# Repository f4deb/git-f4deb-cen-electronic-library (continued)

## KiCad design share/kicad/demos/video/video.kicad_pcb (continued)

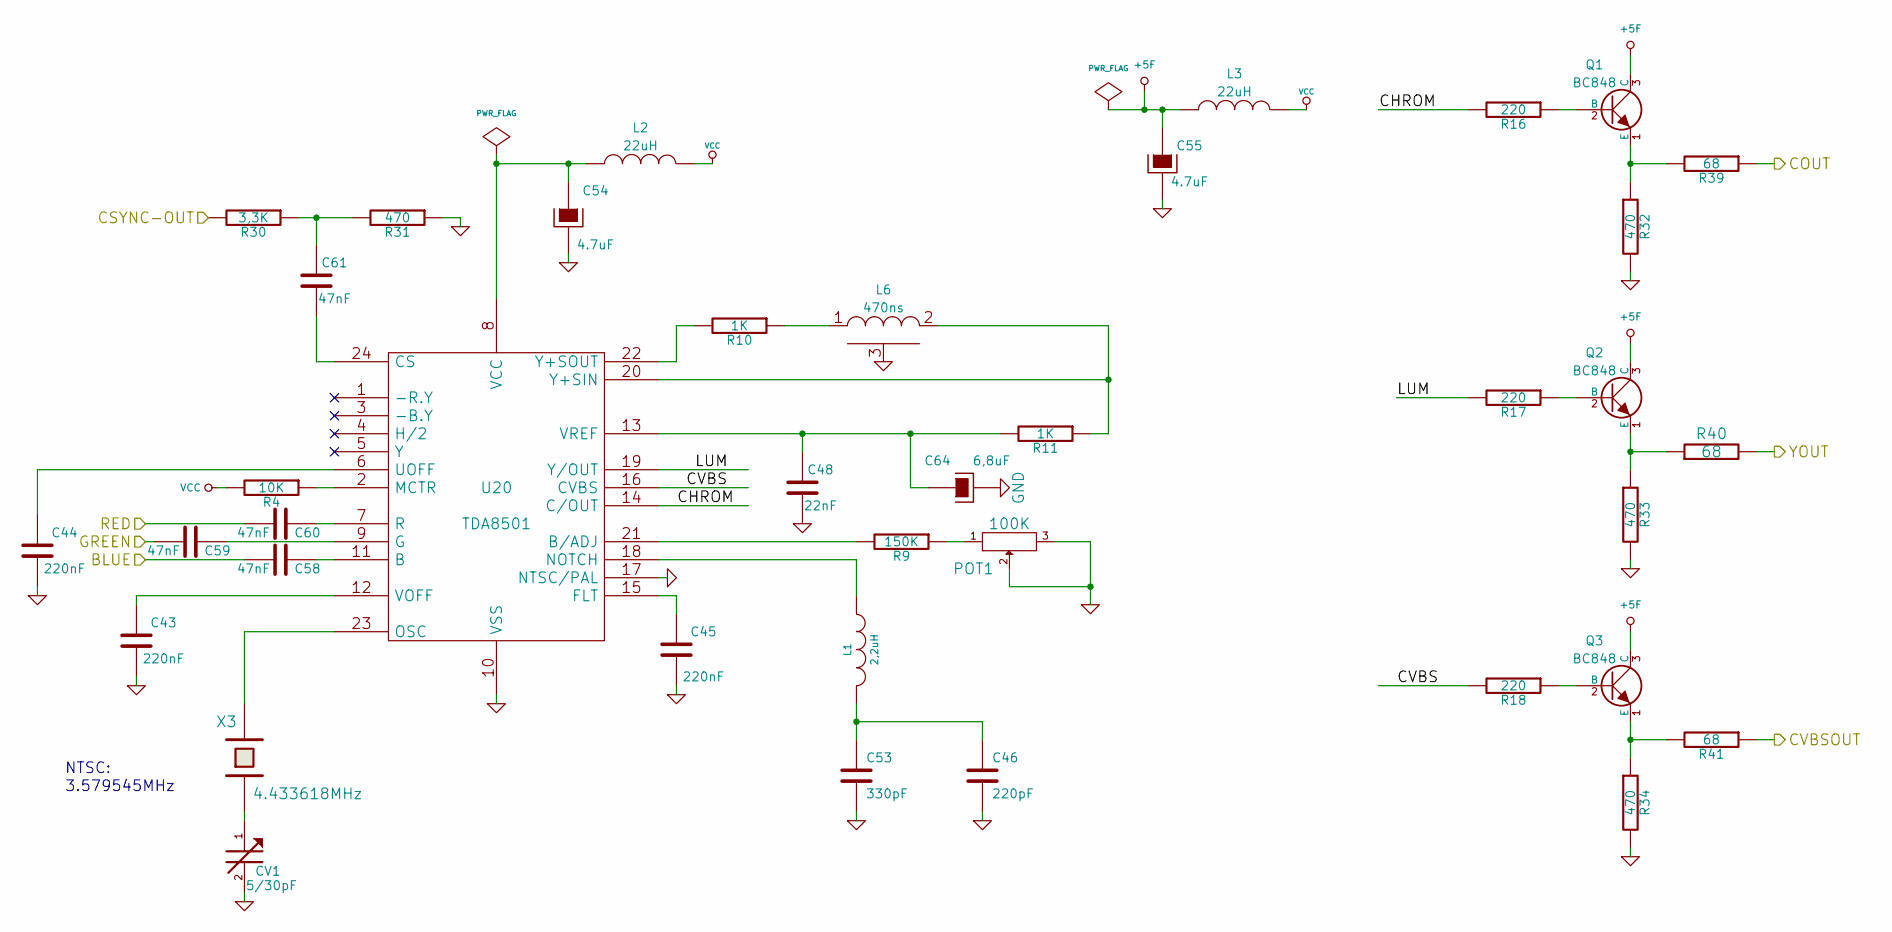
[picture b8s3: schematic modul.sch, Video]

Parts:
C43, C44, C45: 220nF; SM1206
C46: 220pF; SM1206
C48: 22nF; SM1206
C53: 330pF; SM1206
C54: 4.7uF; SM1206
C55: 4.7uF; SM1210L
C58, C59, C60, C61: 47nF; SM1206
C64: 6,8uF; SM1210L
CV1: 5/30pF; CV3-30PF
L1: 2,2uH; SM1812
L2, L3: 22uH; SM1812
L6: 470ns; LRTDK
POT1: 100K; POT_CMS
Q1, Q2, Q3: BC848; SOT23EBC
R4: 10K; SM1206
R9: 150K; SM1206
R10, R11: 1K; SM1206
R16, R17, R18: 220; SM1206
R30: 3,3K; SM1206
R31, R32, R33, R34: 470; SM1206
R39, R40, R41: 68; SM1206
U20: TDA8501; SO24E
X3: 4.433618MHz; HC-18UH

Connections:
+5F: C55.1, L3.2, Q1.3 (C), Q2.3 (C), Q3.3 (C)
/ESVIDEO-RVB/BLUE: C60.2; also elsewhere on the board
/ESVIDEO-RVB/GREEN: C59.2; also elsewhere on the board
/graphic/CSYNC-OUT: R30.2; also elsewhere on the board
/modul/BLEU: C58.2; also elsewhere on the board
/modul/CHROM: R16.2, U20.14 (C/OUT)
/modul/COUT: R39.1; also elsewhere on the board
/modul/CVBS: R18.2, U20.16 (CVBS)
/modul/CVBSOUT: R41.1; also elsewhere on the board
/modul/LUM: R17.2, U20.19 (Y/OUT)
/modul/YOUT: R40.2; also elsewhere on the board
GND: C43.2, C44.2, C45.2, C46.2, C48.1, C53.2, C54.2, C55.2, C64.2, CV1.2, L6.3 (COMMUN), POT1.2, POT1.3, R31.1, R32.2, R33.2, R34.2, U20.10 (VSS), U20.17 (NTSC/PAL); also elsewhere on the board
unnamed: C43.1, U20.12 (VOFF)
unnamed: C44.1, U20.6 (UOFF)
unnamed: C45.1, U20.15 (FLT)
unnamed: C46.1, C53.1, L1.2
unnamed: C48.2, C64.1, R11.2, U20.13 (VREF)
unnamed: C54.1, L2.2, U20.8 (VCC)
unnamed: C58.1, U20.11 (B)
unnamed: C59.1, U20.9 (G)
unnamed: C60.1, U20.7 (R)
unnamed: C61.1, R30.1, R31.2
unnamed: C61.2, U20.24 (CS)
unnamed: CV1.1, X3.1
unnamed: L1.1, U20.18 (NOTCH)
unnamed: L6.1, R10.1
unnamed: L6.2, R11.1, U20.20 (Y+SIN)
unnamed: POT1.1, R9.1
unnamed: Q1.1 (E), R32.1, R39.2
unnamed: Q1.2 (B), R16.1
unnamed: Q2.1 (E), R33.1, R40.1
unnamed: Q2.2 (B), R17.1
unnamed: Q3.1 (E), R34.1, R41.2
unnamed: Q3.2 (B), R18.1
unnamed: R4.1, U20.2 (MCTR)
unnamed: R9.2, U20.21 (B/ADJ)
unnamed: R10.2, U20.22 (Y+SOUT)
unnamed: U20.23 (OSC), X3.2
VCC: L2.1, L3.1, R4.2; also elsewhere on the board

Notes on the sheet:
NTSC:
3.579545MHz

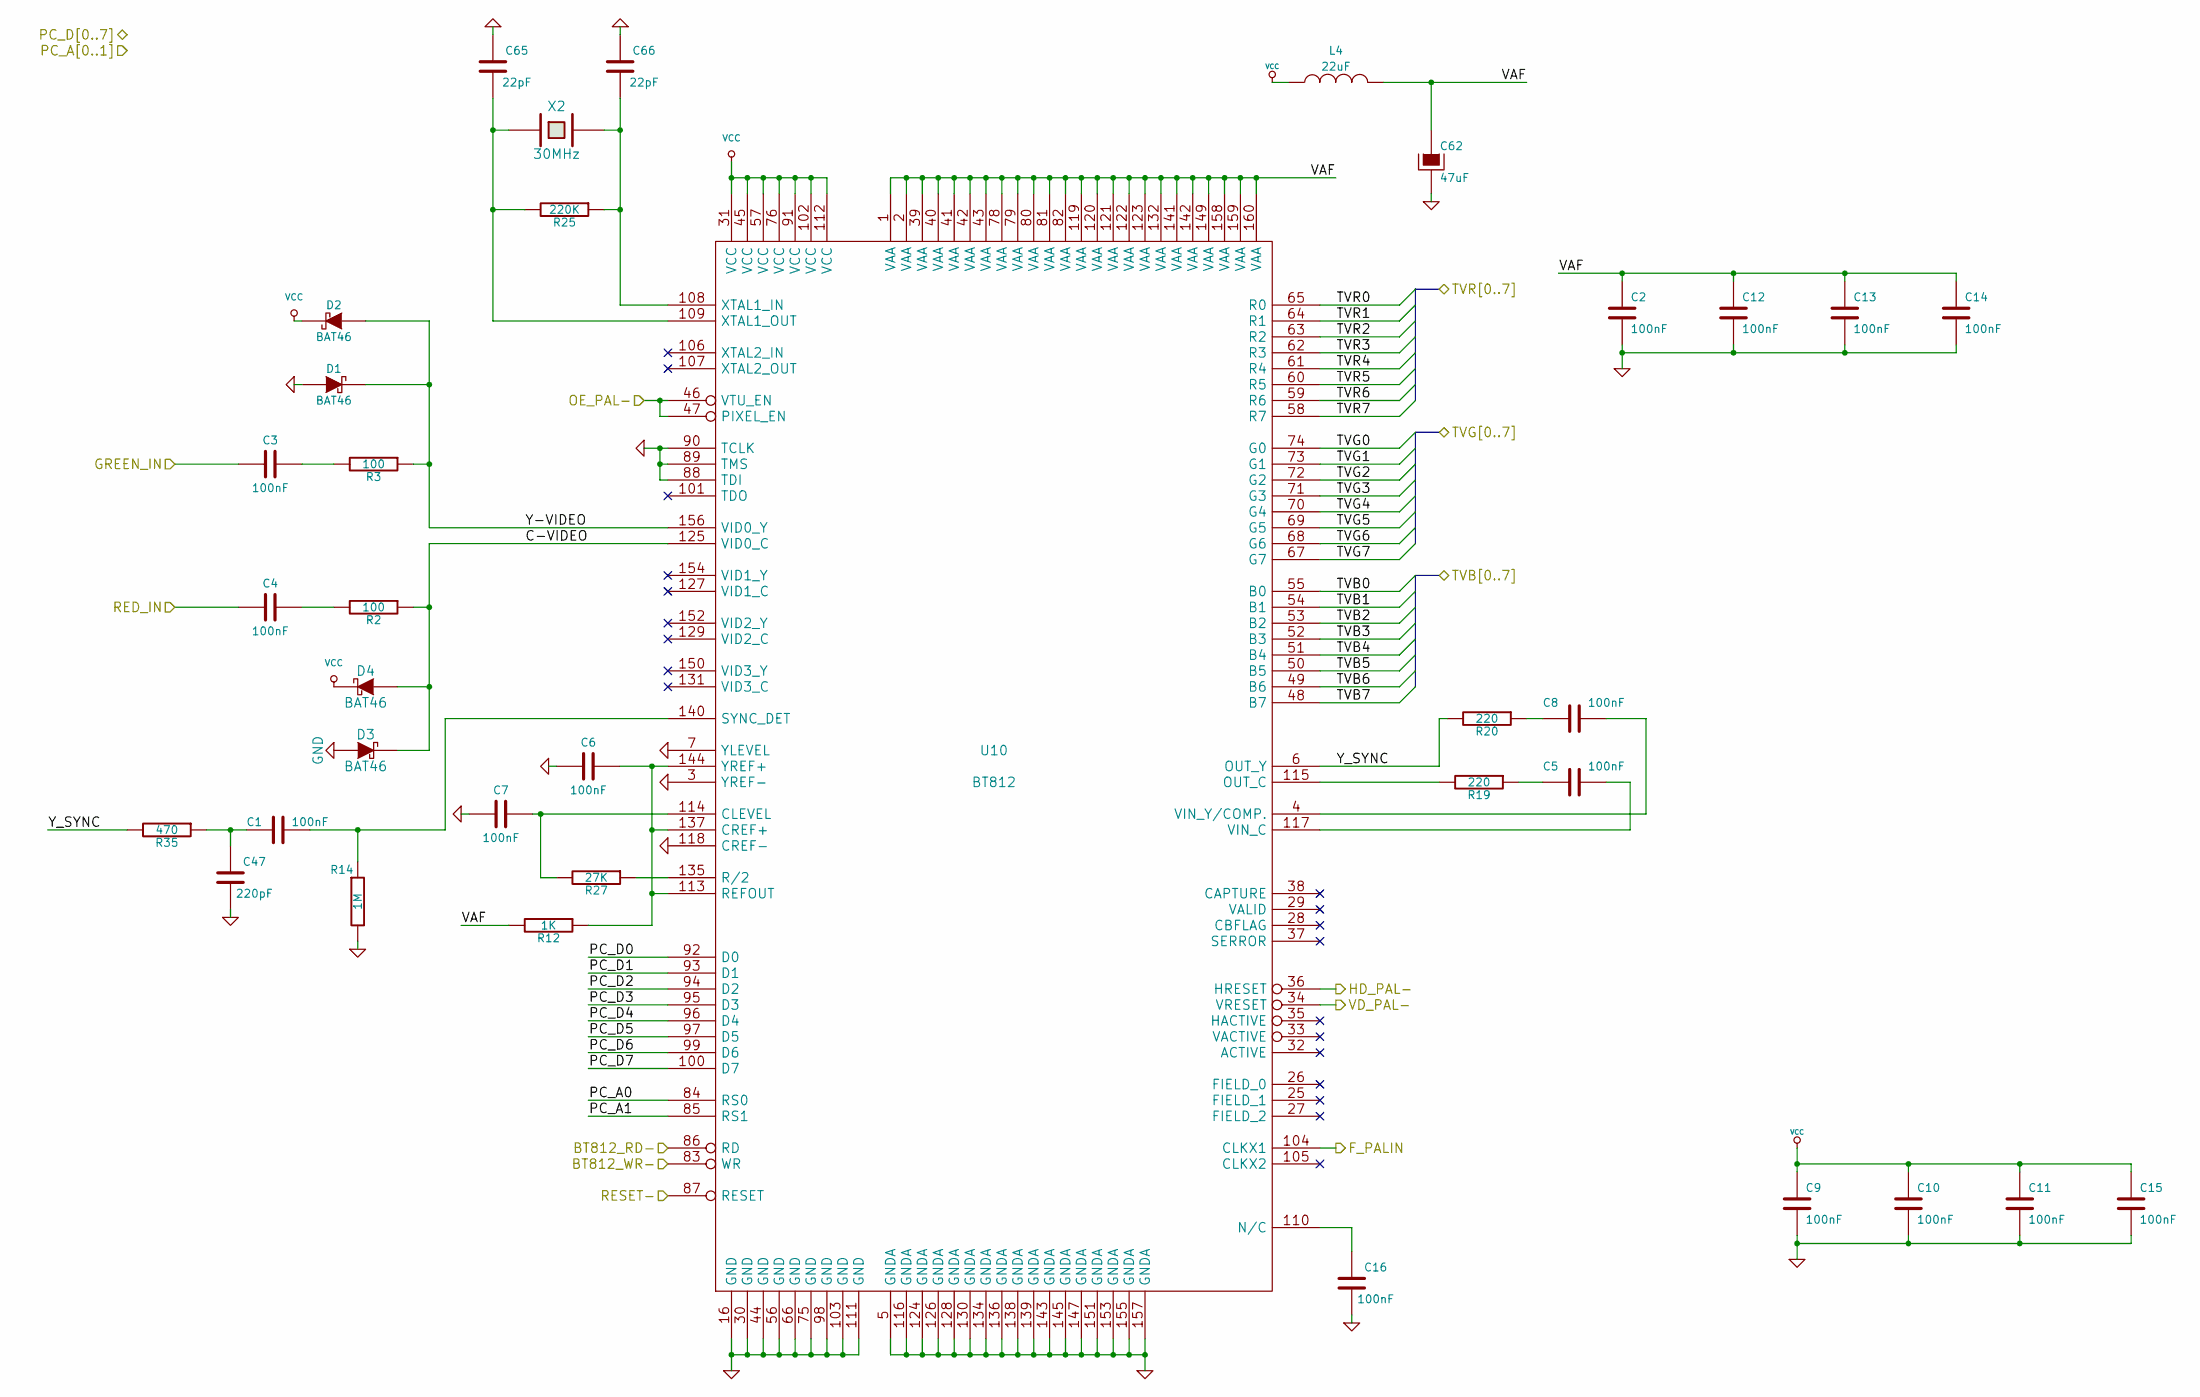
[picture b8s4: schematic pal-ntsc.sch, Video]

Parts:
C1, C2, C3, C4, C5, C6, C7, C8, C9, C10, C11, C12, C13, C14, C15, C16: 100nF; SM1206
C47: 220pF; SM1206
C62: 47uF; SM1210L
C65, C66: 22pF; SM1206
D1, D2, D3, D4: BAT46; D3
L4: 22uF; SM1812
R2, R3: 100; SM1206
R12: 1K; SM1206
R14: 1M; SM1206
R19, R20: 220; SM1206
R25: 220K; SM1206
R27: 27K; SM1206
R35: 470; SM1206
U10: BT812; PQFP160
X2: 30MHz; HC-18UV

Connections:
/ESVIDEO-RVB/DPC0: U10.92 (D0); also elsewhere on the board
/ESVIDEO-RVB/DPC1: U10.93 (D1); also elsewhere on the board
/ESVIDEO-RVB/DPC2: U10.94 (D2); also elsewhere on the board
/ESVIDEO-RVB/DPC3: U10.95 (D3); also elsewhere on the board
/ESVIDEO-RVB/DPC4: U10.96 (D4); also elsewhere on the board
/ESVIDEO-RVB/DPC5: U10.97 (D5); also elsewhere on the board
/ESVIDEO-RVB/DPC6: U10.99 (D6); also elsewhere on the board
/ESVIDEO-RVB/DPC7: U10.100 (D7); also elsewhere on the board
/ESVIDEO-RVB/GREEN_IN: C3.2; also elsewhere on the board
/ESVIDEO-RVB/OE_PAL-: U10.46 (VTU_EN), U10.47 (PIXEL_EN); also elsewhere on the board
/ESVIDEO-RVB/PCA0: U10.84 (RS0); also elsewhere on the board
/ESVIDEO-RVB/PCA1: U10.85 (RS1); also elsewhere on the board
/ESVIDEO-RVB/RED_IN: C4.2; also elsewhere on the board
/ESVIDEO-RVB/TVB0: U10.55 (B0); also elsewhere on the board
/ESVIDEO-RVB/TVB1: U10.54 (B1); also elsewhere on the board
/ESVIDEO-RVB/TVB2: U10.53 (B2); also elsewhere on the board
/ESVIDEO-RVB/TVB3: U10.52 (B3); also elsewhere on the board
/ESVIDEO-RVB/TVB4: U10.51 (B4); also elsewhere on the board
/ESVIDEO-RVB/TVB5: U10.50 (B5); also elsewhere on the board
/ESVIDEO-RVB/TVB6: U10.49 (B6); also elsewhere on the board
/ESVIDEO-RVB/TVB7: U10.48 (B7); also elsewhere on the board
/ESVIDEO-RVB/TVG0: U10.74 (G0); also elsewhere on the board
/ESVIDEO-RVB/TVG1: U10.73 (G1); also elsewhere on the board
/ESVIDEO-RVB/TVG2: U10.72 (G2); also elsewhere on the board
/ESVIDEO-RVB/TVG3: U10.71 (G3); also elsewhere on the board
/ESVIDEO-RVB/TVG4: U10.70 (G4); also elsewhere on the board
/ESVIDEO-RVB/TVG5: U10.69 (G5); also elsewhere on the board
/ESVIDEO-RVB/TVG6: U10.68 (G6); also elsewhere on the board
/ESVIDEO-RVB/TVG7: U10.67 (G7); also elsewhere on the board
/ESVIDEO-RVB/TVR0: U10.65 (R0); also elsewhere on the board
/ESVIDEO-RVB/TVR1: U10.64 (R1); also elsewhere on the board
/ESVIDEO-RVB/TVR2: U10.63 (R2); also elsewhere on the board
/ESVIDEO-RVB/TVR3: U10.62 (R3); also elsewhere on the board
/ESVIDEO-RVB/TVR4: U10.61 (R4); also elsewhere on the board
/ESVIDEO-RVB/TVR5: U10.60 (R5); also elsewhere on the board
/ESVIDEO-RVB/TVR6: U10.59 (R6); also elsewhere on the board
/ESVIDEO-RVB/TVR7: U10.58 (R7); also elsewhere on the board
/graphic/BT812_RD-: U10.86 (RD); also elsewhere on the board
/graphic/BT812_WR-: U10.83 (WR); also elsewhere on the board
/graphic/F_PALIN: U10.104 (CLKX1); also elsewhere on the board
/graphic/HD_PAL-: U10.36 (HRESET); also elsewhere on the board
/graphic/VD_PAL-: U10.34 (VRESET); also elsewhere on the board
/pal-ntsc.sch/C-VIDEO: D3.2 (K), D4.1 (A), R2.1, U10.125 (VID0_C)
/pal-ntsc.sch/RESET-: U10.87 (RESET); also elsewhere on the board
/pal-ntsc.sch/VAF: C2.1, C12.1, C13.1, C14.1, C62.1, L4.2, R12.2, U10.1 (VAA), U10.2 (VAA), U10.39 (VAA), U10.40 (VAA), U10.41 (VAA), U10.42 (VAA), U10.43 (VAA), U10.78 (VAA), U10.79 (VAA), U10.80 (VAA), U10.81 (VAA), U10.82 (VAA), U10.119 (VAA), U10.120 (VAA), U10.121 (VAA), U10.122 (VAA), U10.123 (VAA), U10.132 (VAA), U10.141 (VAA), U10.142 (VAA), U10.149 (VAA), U10.158 (VAA), U10.159 (VAA), U10.160 (VAA)
/pal-ntsc.sch/Y-VIDEO: D1.2 (K), D2.1 (A), R3.1, U10.156 (VID0_Y)
/pal-ntsc.sch/Y_SYNC: R20.2, R35.2, U10.6 (OUT_Y)
GND: C2.2, C6.2, C7.2, C9.2, C10.2, C11.2, C12.2, C13.2, C14.2, C15.2, C16.2, C47.2, C62.2, C65.1, C66.1, D1.1 (A), D3.1 (A), R14.2, U10.3 (YREF-), U10.5 (GNDA), U10.7 (YLEVEL), U10.16 (GND), U10.30 (GND), U10.44 (GND), U10.56 (GND), U10.66 (GND), U10.75 (GND), U10.88 (TDI), U10.89 (TMS), U10.90 (TCLK), U10.98 (GND), U10.103 (GND), U10.111 (GND), U10.116 (GNDA), U10.118 (CREF-), U10.124 (GNDA), U10.126 (GNDA), U10.128 (GNDA), U10.130 (GNDA), U10.134 (GNDA), U10.136 (GNDA), U10.138 (GNDA), U10.139 (GNDA), U10.143 (GNDA), U10.145 (GNDA), U10.147 (GNDA), U10.151 (GNDA), U10.153 (GNDA), U10.155 (GNDA), U10.157 (GNDA); also elsewhere on the board
unnamed: C1.1, C47.1, R35.1
unnamed: C1.2, R14.1, U10.140 (SYNC_DET)
unnamed: C3.1, R3.2
unnamed: C4.1, R2.2
unnamed: C5.1, U10.117 (VIN_C)
unnamed: C5.2, R19.1
unnamed: C6.1, R12.1, U10.113 (REFOUT), U10.137 (CREF+), U10.144 (YREF+)
unnamed: C7.1, R27.2, U10.114 (CLEVEL)
unnamed: C8.1, U10.4 (VIN_Y/COMP.)
unnamed: C8.2, R20.1
unnamed: C16.1, U10.110 (N/C)
unnamed: C65.2, R25.2, U10.109 (XTAL1_OUT), X2.1
unnamed: C66.2, R25.1, U10.108 (XTAL1_IN), X2.2
unnamed: R19.2, U10.115 (OUT_C)
unnamed: R27.1, U10.135 (R/2)
VCC: C9.1, C10.1, C11.1, C15.1, D2.2 (K), D4.2 (K), L4.1, U10.31 (VCC), U10.45 (VCC), U10.57 (VCC), U10.76 (VCC), U10.91 (VCC), U10.102 (VCC), U10.112 (VCC); also elsewhere on the board

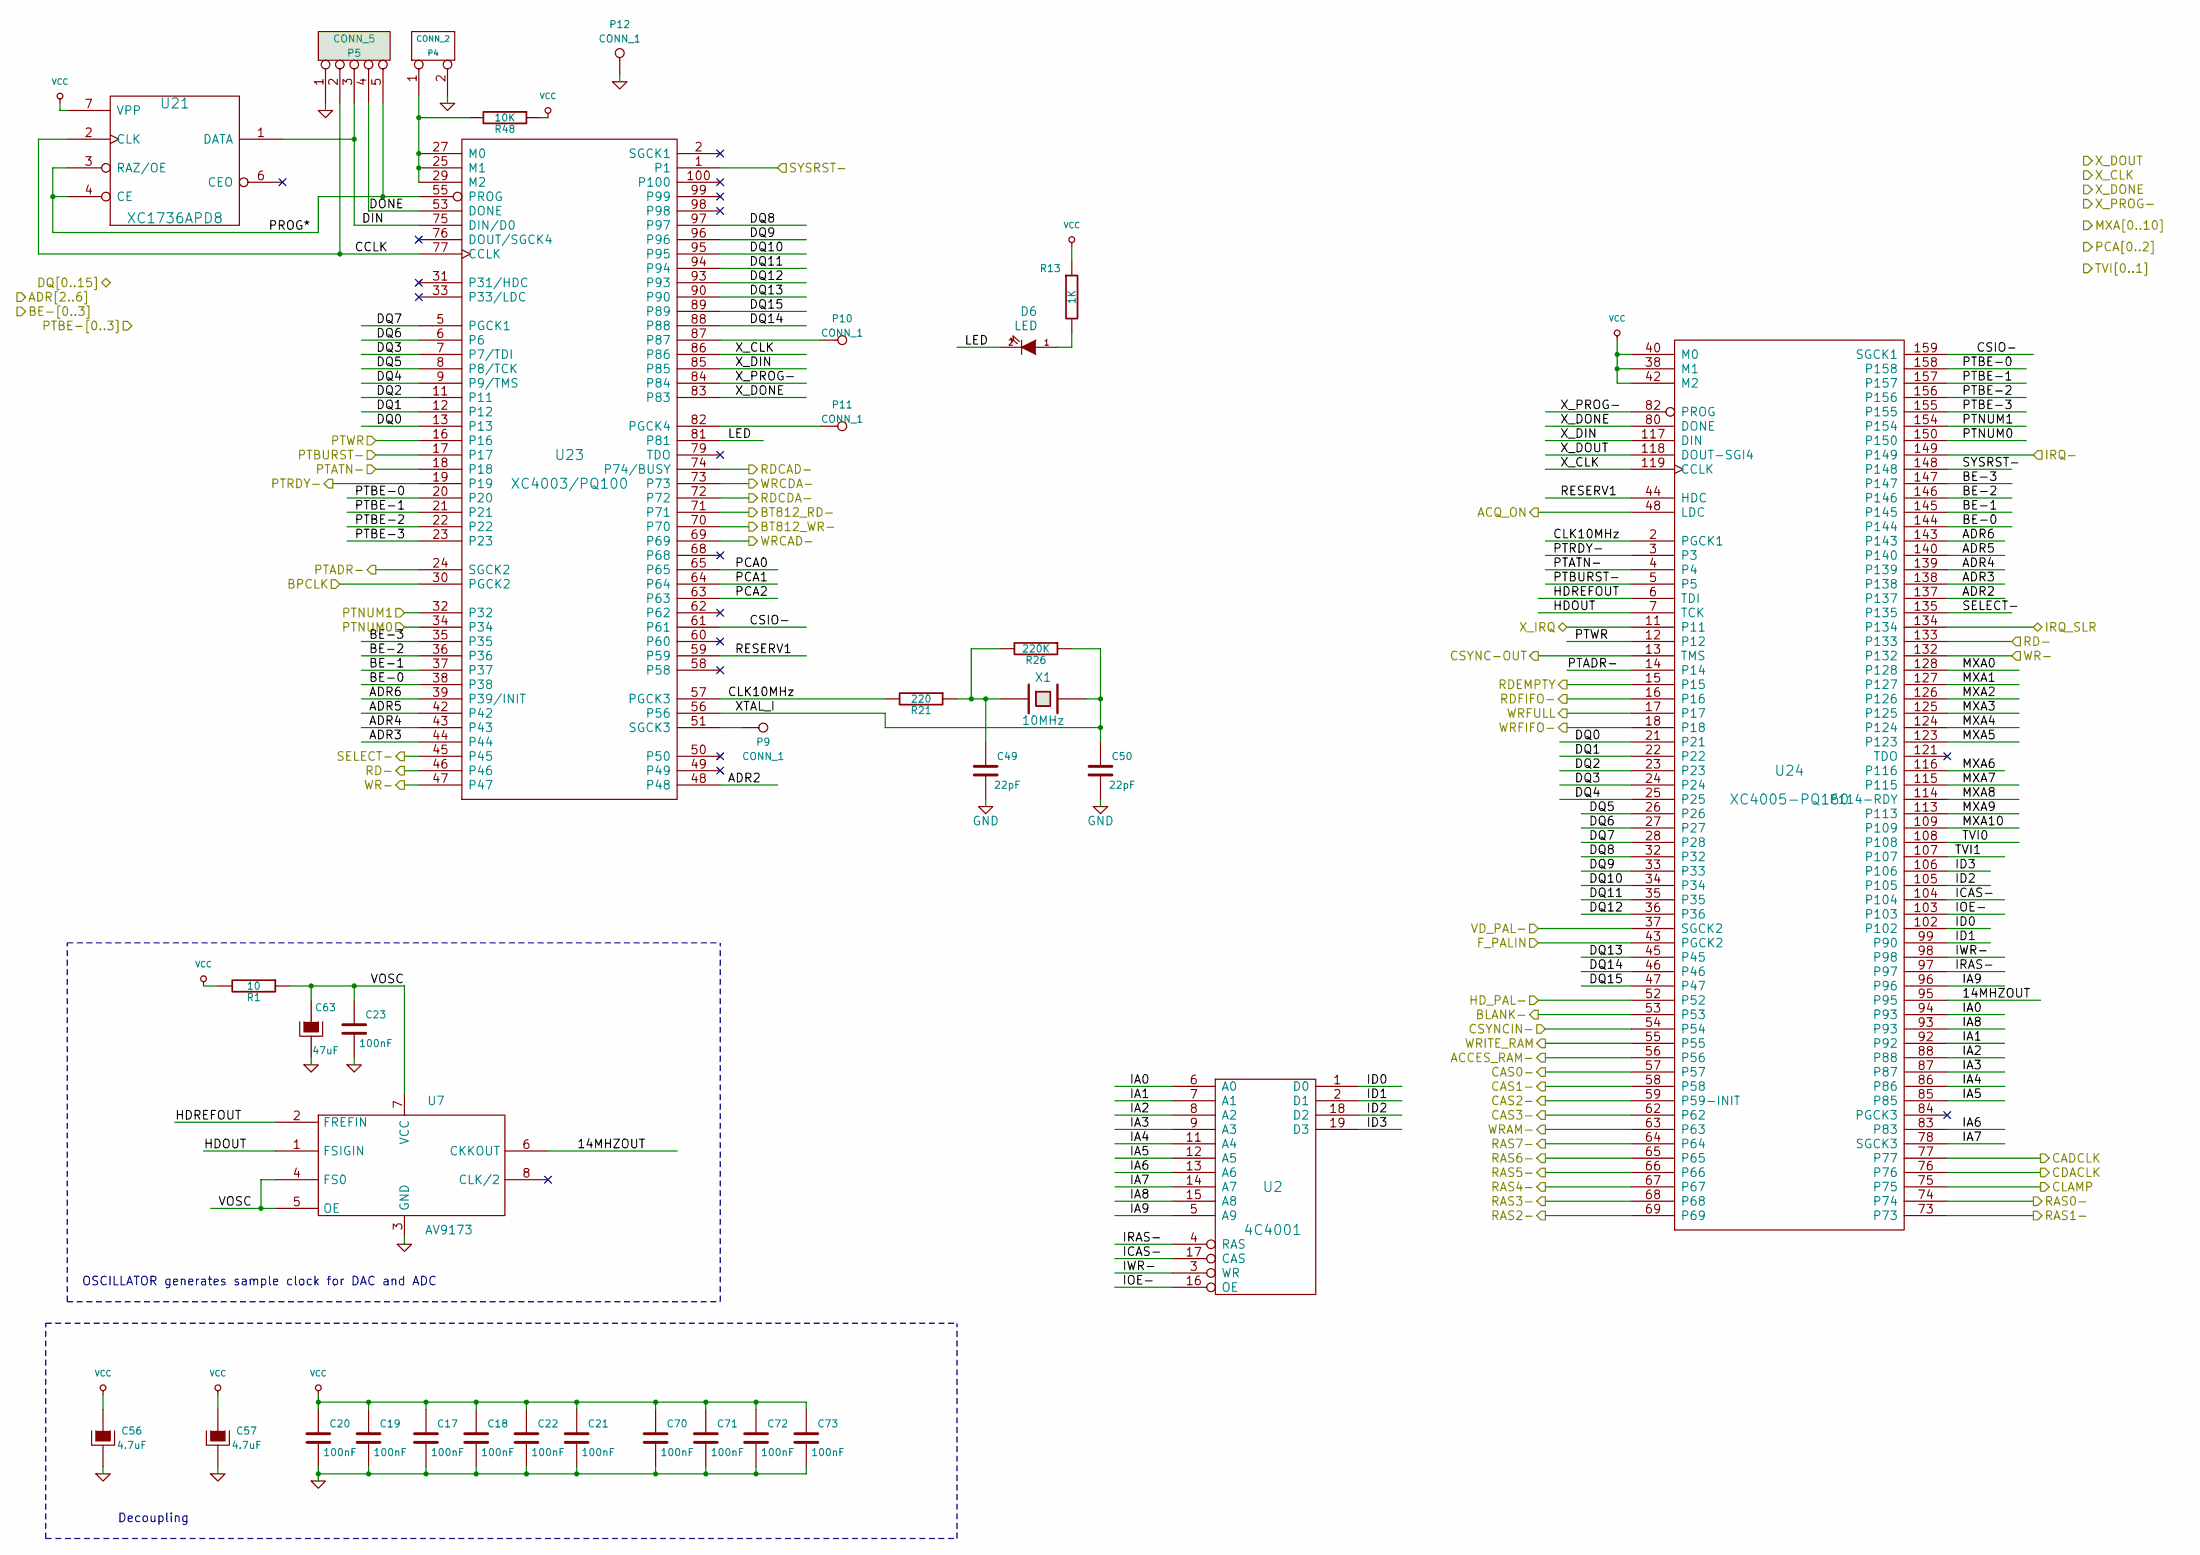
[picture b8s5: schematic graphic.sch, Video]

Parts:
C17, C18, C19, C20, C21, C22, C23, C70, C71, C72, C73: 100nF; SM1206
C49, C50: 22pF; C1
C56: 4.7uF; SM1812L
C57: 4.7uF; SM1210L
C63: 47uF; SM1210L
D6: LED; LEDV
P4: CONN_2; SIL-2
P5: CONN_5; PIN_ARRAY_5x1
P9, P10, P11: CONN_1; PINTST
P12: CONN_1; TESTPOINT
R1: 10; SM1206
R13: 1K; SM1206
R21: 220; SM1206
R26: 220K; SM1206
R48: 10K; SM1206
U2: 4C4001; SO28
U7: AV9173; SO8E
U21: XC1736APD8; DIP-8__300
U23: XC4003/PQ100; PQFP100
U24: XC4005-PQ160; PQFP160
X1: 10MHz; HC-18UV

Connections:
/ESVIDEO-RVB/BLANK-: U24.53; also elsewhere on the board
/ESVIDEO-RVB/CLAMP: U24.75; also elsewhere on the board
/ESVIDEO-RVB/CSYNCIN-: U24.54; also elsewhere on the board
/ESVIDEO-RVB/DPC0: U23.13, U24.21; also elsewhere on the board
/ESVIDEO-RVB/DPC1: U23.12, U24.22; also elsewhere on the board
/ESVIDEO-RVB/DPC2: U23.11, U24.23; also elsewhere on the board
/ESVIDEO-RVB/DPC3: U23.7 (P7/TDI), U24.24; also elsewhere on the board
/ESVIDEO-RVB/DPC4: U23.9 (P9/TMS), U24.25; also elsewhere on the board
/ESVIDEO-RVB/DPC5: U23.8 (P8/TCK), U24.26; also elsewhere on the board
/ESVIDEO-RVB/DPC6: U23.6, U24.27; also elsewhere on the board
/ESVIDEO-RVB/DPC7: U23.5 (PGCK1), U24.28; also elsewhere on the board
/ESVIDEO-RVB/PCA0: U23.65; also elsewhere on the board
/ESVIDEO-RVB/PCA1: U23.64; also elsewhere on the board
/ESVIDEO-RVB/PCA2: U23.63; also elsewhere on the board
/ESVIDEO-RVB/RDCAD-: U23.74 (P74/BUSY); also elsewhere on the board
/ESVIDEO-RVB/RDCDA-: U23.72; also elsewhere on the board
/ESVIDEO-RVB/TVI0: U24.108; also elsewhere on the board
/ESVIDEO-RVB/TVI1: U24.107; also elsewhere on the board
/ESVIDEO-RVB/WRCAD-: U23.69; also elsewhere on the board
/ESVIDEO-RVB/WRCDA-: U23.73; also elsewhere on the board
/RAMS/CAS0-: U24.57; also elsewhere on the board
/RAMS/CAS1-: U24.58; also elsewhere on the board
/RAMS/CAS2-: U24.59 (P59-INIT); also elsewhere on the board
/RAMS/CAS3-: U24.62; also elsewhere on the board
/RAMS/MXA0: U24.128; also elsewhere on the board
/RAMS/MXA1: U24.127; also elsewhere on the board
/RAMS/MXA2: U24.126; also elsewhere on the board
/RAMS/MXA3: U24.125; also elsewhere on the board
/RAMS/MXA4: U24.124; also elsewhere on the board
/RAMS/MXA5: U24.123; also elsewhere on the board
/RAMS/MXA6: U24.116; also elsewhere on the board
/RAMS/MXA7: U24.115; also elsewhere on the board
/RAMS/MXA8: U24.114 (P114-RDY); also elsewhere on the board
/RAMS/MXA9: U24.113; also elsewhere on the board
/RAMS/MXA10: U24.109; also elsewhere on the board
/RAMS/RAS0-: U24.74; also elsewhere on the board
/RAMS/RAS1-: U24.73; also elsewhere on the board
/RAMS/RAS2-: U24.69; also elsewhere on the board
/RAMS/RAS3-: U24.68; also elsewhere on the board
/RAMS/RAS4-: U24.67; also elsewhere on the board
/RAMS/RAS5-: U24.66; also elsewhere on the board
/RAMS/RAS6-: U24.65; also elsewhere on the board
/RAMS/RAS7-: U24.64; also elsewhere on the board
/RAMS/WRAM-: U24.63; also elsewhere on the board
/buspci.sch/ADR2: U23.48, U24.137; also elsewhere on the board
/buspci.sch/ADR3: U23.44, U24.138; also elsewhere on the board
/buspci.sch/ADR4: U23.43, U24.139; also elsewhere on the board
/buspci.sch/ADR5: U23.42, U24.140; also elsewhere on the board
/buspci.sch/ADR6: U23.39 (P39/INIT), U24.143; also elsewhere on the board
/buspci.sch/BE-0: U23.38, U24.144; also elsewhere on the board
/buspci.sch/BE-1: U23.37, U24.145; also elsewhere on the board
/buspci.sch/BE-2: U23.36, U24.146; also elsewhere on the board
/buspci.sch/BE-3: U23.35, U24.147; also elsewhere on the board
/buspci.sch/BPCLK: U23.30 (PGCK2); also elsewhere on the board
/buspci.sch/IRQ-: U24.149; also elsewhere on the board
/buspci.sch/PTADR-: U23.24 (SGCK2), U24.14; also elsewhere on the board
/buspci.sch/PTATN-: U23.18, U24.4; also elsewhere on the board
/buspci.sch/PTBE-0: U23.20, U24.158; also elsewhere on the board
/buspci.sch/PTBE-1: U23.21, U24.157; also elsewhere on the board
/buspci.sch/PTBE-2: U23.22, U24.156; also elsewhere on the board
/buspci.sch/PTBE-3: U23.23, U24.155; also elsewhere on the board
/buspci.sch/PTBURST-: U23.17, U24.5; also elsewhere on the board
/buspci.sch/PTNUM0: U23.34, U24.150; also elsewhere on the board
/buspci.sch/PTNUM1: U23.32, U24.154; also elsewhere on the board
/buspci.sch/PTRDY-: U23.19, U24.3; also elsewhere on the board
/buspci.sch/PTWR: U23.16, U24.12; also elsewhere on the board
/buspci.sch/RD-: U23.46, U24.133; also elsewhere on the board
/buspci.sch/RDEMPTY: U24.15; also elsewhere on the board
/buspci.sch/RDFIFO-: U24.16; also elsewhere on the board
/buspci.sch/SELECT-: U23.45, U24.135; also elsewhere on the board
/buspci.sch/WR-: U23.47, U24.132; also elsewhere on the board
/buspci.sch/WRFIFO-: U24.18; also elsewhere on the board
/buspci.sch/WRFULL: U24.17; also elsewhere on the board
/buspci.sch/X_IRQ: U24.11; also elsewhere on the board
/graphic/14MHZOUT: U7.6 (CKKOUT), U24.95
/graphic/ACCES_RAM-: U24.56; also elsewhere on the board
/graphic/ACQ_ON: U24.48 (LDC); also elsewhere on the board
/graphic/BT812_RD-: U23.71; also elsewhere on the board
/graphic/BT812_WR-: U23.70; also elsewhere on the board
/graphic/CADCLK: U24.77; also elsewhere on the board
/graphic/CCLK: P5.2, U21.2 (CLK), U23.77 (CCLK)
/graphic/CDACLK: U24.76; also elsewhere on the board
/graphic/CLK10MHz: R21.2, U23.57 (PGCK3), U24.2 (PGCK1)
/graphic/CSIO-: U23.61, U24.159 (SGCK1)
/graphic/CSYNC-OUT: U24.13 (TMS); also elsewhere on the board
/graphic/DIN: P5.3, U21.1 (DATA), U23.75 (DIN/D0)
/graphic/DONE: P5.4, U23.53 (DONE)
/graphic/F_PALIN: U24.43 (PGCK2); also elsewhere on the board
/graphic/HDOUT: U7.1 (FSIGIN), U24.7 (TCK)
/graphic/HDREFOUT: U7.2 (FREFIN), U24.6 (TDI)
/graphic/HD_PAL-: U24.52; also elsewhere on the board
/graphic/IA0: U2.6 (A0), U24.94 (P93)
/graphic/IA1: U2.7 (A1), U24.92
/graphic/IA2: U2.8 (A2), U24.88
/graphic/IA3: U2.9 (A3), U24.87
/graphic/IA4: U2.11 (A4), U24.86
/graphic/IA5: U2.12 (A5), U24.85
/graphic/IA6: U2.13 (A6), U24.83
/graphic/IA7: U2.14 (A7), U24.78 (SGCK3)
/graphic/IA8: U2.15 (A8), U24.93
/graphic/IA9: U2.5 (A9), U24.96
/graphic/ICAS-: U2.17 (CAS), U24.104
/graphic/ID0: U2.1 (D0), U24.102
/graphic/ID1: U2.2 (D1), U24.99 (P90)
/graphic/ID2: U2.18 (D2), U24.105
/graphic/ID3: U2.19 (D3), U24.106
/graphic/IOE-: U2.16 (OE), U24.103
/graphic/IRAS-: U2.4 (RAS), U24.97
/graphic/IRQ_SLR: U24.134; also elsewhere on the board
/graphic/IWR-: U2.3 (WR), U24.98
/graphic/LED: D6.2 (K), U23.81
/graphic/PROG*: P5.5, U21.3 (RAZ/OE), U21.4 (CE), U23.55 (PROG)
/graphic/RESERV1: U23.59, U24.44 (HDC)
/graphic/VD_PAL-: U24.37 (SGCK2); also elsewhere on the board
/graphic/VOSC: C23.1, C63.1, R1.1, U7.4 (FS0), U7.5 (OE), U7.7 (VCC)
/graphic/XTAL_I: C50.1, R26.1, U23.56, X1.2
/graphic/X_CLK: U23.86, U24.119 (CCLK); also elsewhere on the board
/graphic/X_DIN: U23.85, U24.117 (DIN)
/graphic/X_DONE: U23.83, U24.80 (DONE); also elsewhere on the board
/graphic/X_PROG-: U23.84, U24.82 (PROG); also elsewhere on the board
/muxdata/DATA_WR: U24.55; also elsewhere on the board
/muxdata/DPC8: U23.97, U24.32; also elsewhere on the board
/muxdata/DPC9: U23.96, U24.33; also elsewhere on the board
/muxdata/DPC10: U23.95, U24.34; also elsewhere on the board
/muxdata/DPC11: U23.94, U24.35; also elsewhere on the board
/muxdata/DPC12: U23.93, U24.36; also elsewhere on the board
/muxdata/DPC13: U23.90, U24.45; also elsewhere on the board
/muxdata/DPC14: U23.88, U24.46; also elsewhere on the board
/muxdata/DPC15: U23.89, U24.47; also elsewhere on the board
/muxdata/X_DIN: U24.118 (DOUT-SGI4); also elsewhere on the board
/pal-ntsc.sch/RESET-: U23.1, U24.148; also elsewhere on the board
GND: C17.2, C18.2, C19.2, C20.2, C21.2, C22.2, C23.2, C49.2, C50.2, C56.2, C57.2, C63.2, C70.2, C71.2, C72.2, C73.2, P4.2 (PM), P5.1, P12.1, U2.20 (GND), U7.3 (GND), U21.5 (GND), U23.4 (GND), U23.14 (GND), U23.26 (GND), U23.41 (GND), U23.52 (GND), U23.67 (GND), U23.80 (GND), U23.91 (GND), U24.1 (GND), U24.10 (GND), U24.19 (GND), U24.29 (GND), U24.39 (GND), U24.51 (GND), U24.61 (GND), U24.70 (GND), U24.79 (GND), U24.91 (GND), U24.101 (GND), U24.110 (GND), U24.122 (GND), U24.131 (GND), U24.141 (GND), U24.151 (GND); also elsewhere on the board
unnamed: C49.1, R21.1, R26.2, X1.1
unnamed: D6.1 (A), R13.2
unnamed: P4.1, R48.2, U23.25 (M1), U23.27 (M0), U23.29 (M2)
unnamed: P9.1, U23.51 (SGCK3)
unnamed: P10.1, U23.87
unnamed: P11.1, U23.82 (PGCK4)
VCC: C17.1, C18.1, C19.1, C20.1, C21.1, C22.1, C56.1, C57.1, C70.1, C71.1, C72.1, C73.1, R1.2, R13.1, R48.1, U2.10 (VCC), U21.7 (VPP), U21.8 (VCC), U23.3 (VCC), U23.15 (VCC), U23.28 (VCC), U23.40 (VCC), U23.54 (VCC), U23.66 (VCC), U23.78 (VCC), U23.92 (VCC), U24.20 (VCC), U24.38 (M1), U24.40 (M0), U24.41 (VCC), U24.42 (M2), U24.60 (VCC), U24.81 (VCC), U24.100 (VCC), U24.120 (VCC), U24.142 (VCC), U24.160 (VCC); also elsewhere on the board

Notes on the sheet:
Decoupling
OSCILLATOR generates sample clock for DAC and ADC
